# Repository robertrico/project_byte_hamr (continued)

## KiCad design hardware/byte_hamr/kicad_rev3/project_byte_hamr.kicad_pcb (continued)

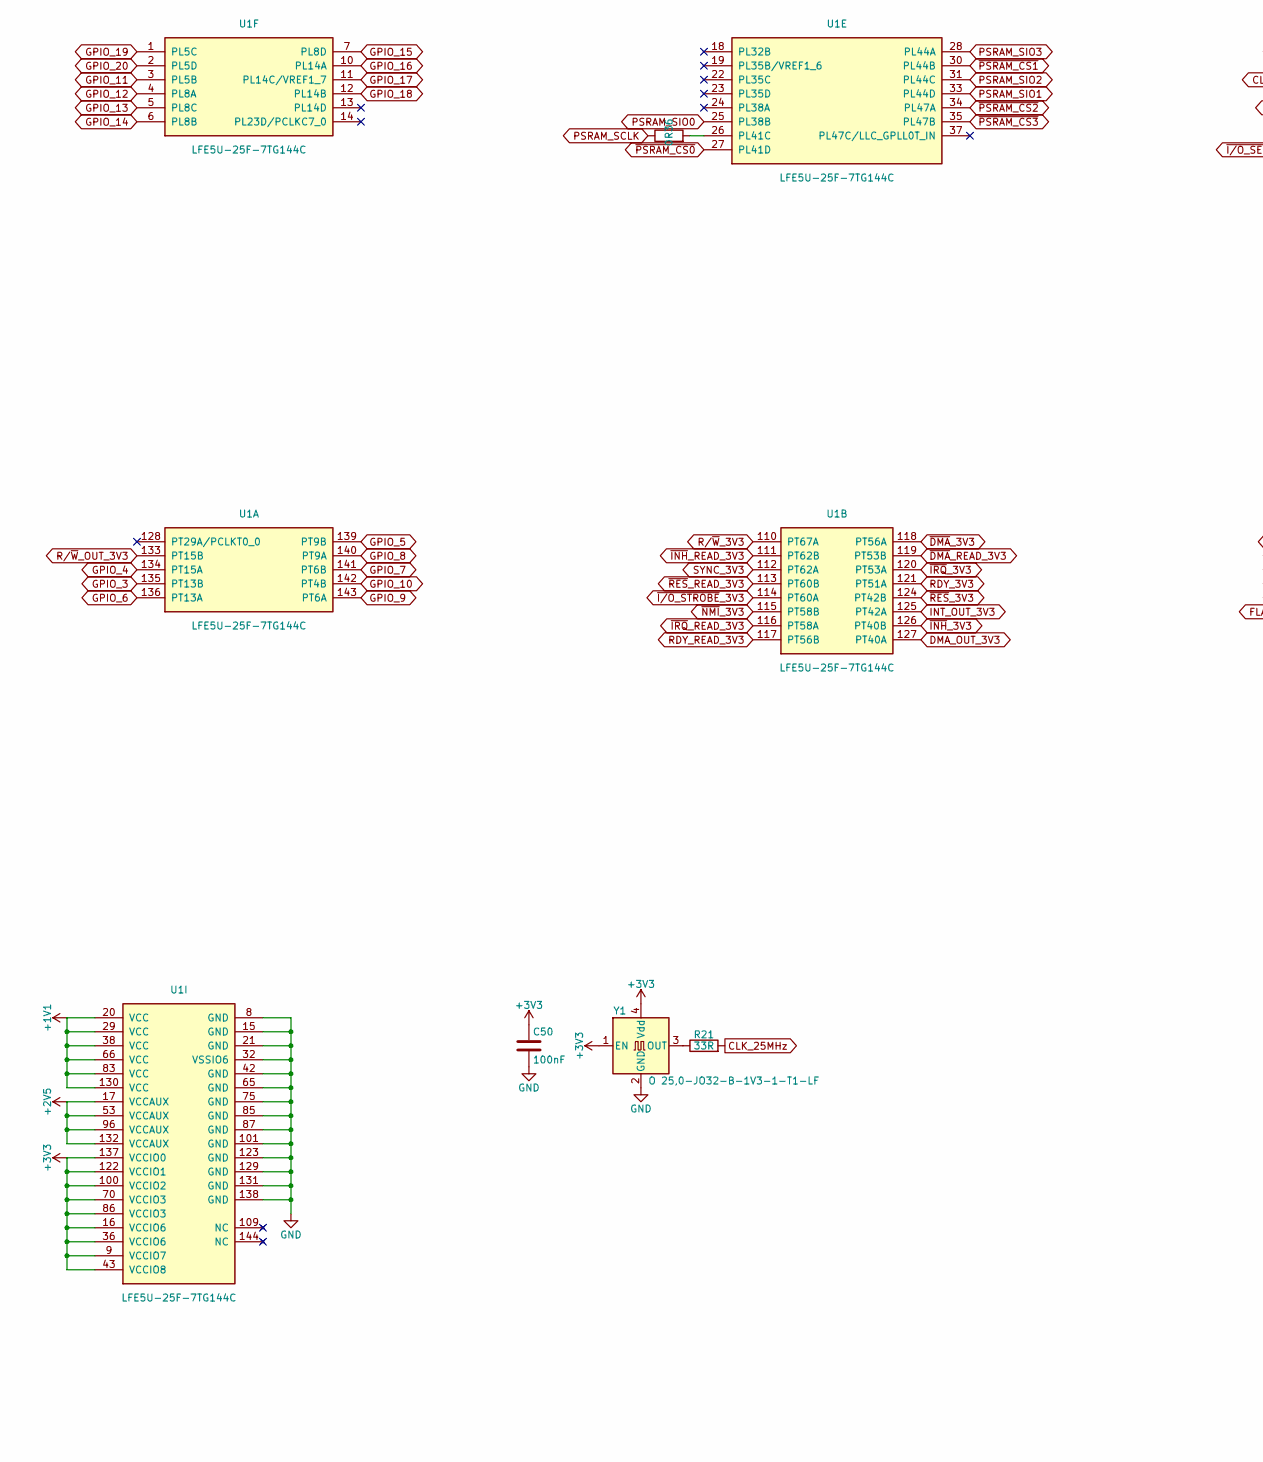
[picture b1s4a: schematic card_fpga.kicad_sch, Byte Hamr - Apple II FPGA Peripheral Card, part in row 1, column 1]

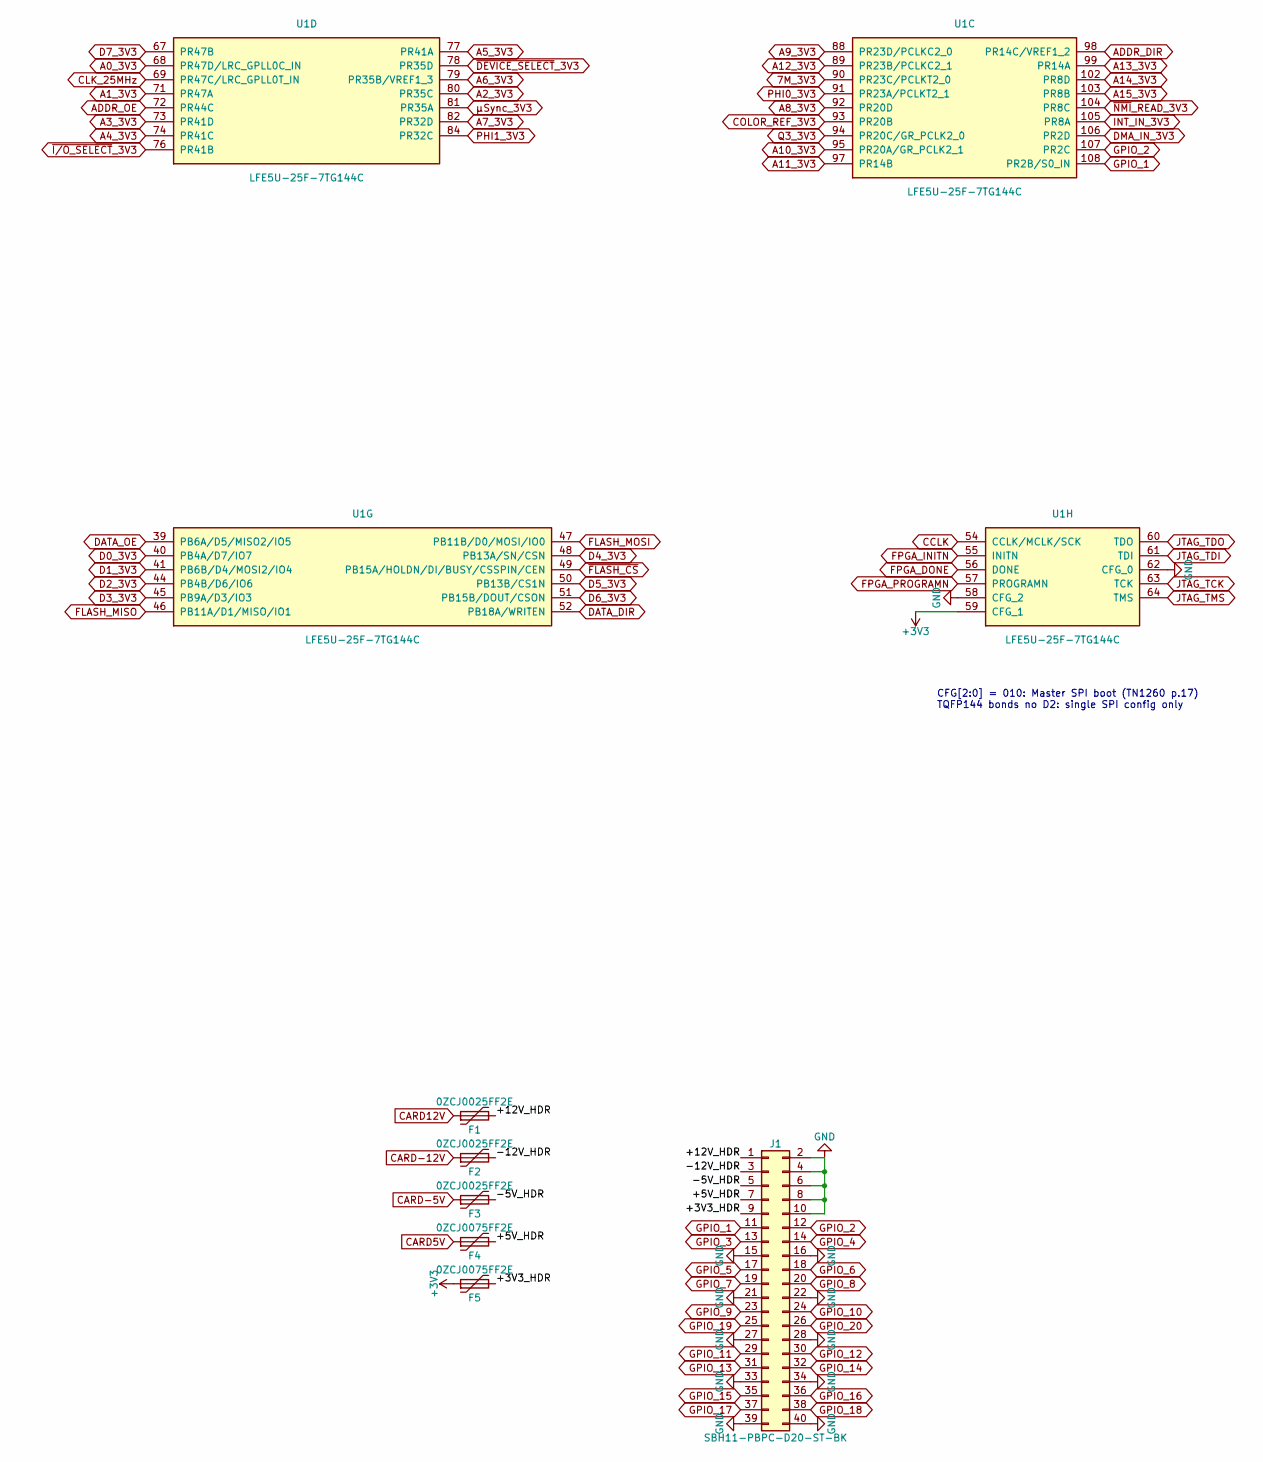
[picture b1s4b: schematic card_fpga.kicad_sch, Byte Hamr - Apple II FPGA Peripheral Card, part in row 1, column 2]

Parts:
C50: 100nF; C_1206_3216Metric; MPN CL31B104KBCNNNC; DigiKey 1276-1017-1-ND
F1, F2, F3: 0ZCJ0025FF2E; Fuse_1206_3216Metric; MPN 0ZCJ0025FF2E; DigiKey 5923-0ZCJ0025FF2ECT-ND
F4, F5: 0ZCJ0075FF2E; Fuse_1206_3216Metric; MPN 0ZCJ0075FF2E; DigiKey 5923-0ZCJ0075FF2ECT-ND
J1: SBH11-PBPC-D20-ST-BK; IDC-Header_2x20_P2.54mm_Vertical; MPN SBH11-PBPC-D20-ST-BK; DigiKey S9175-ND
R21: 33R; R_1206_3216Metric; MPN RMCF1206FT33R0; DigiKey RMCF1206FT33R0CT-ND
R36: 0; R_1206_3216Metric; MPN RMCF1206ZT0R00
U1: LFE5U-25F-7TG144C; LQFP-144_20x20mm_P0.5mm; MPN LFE5U-25F-7TG144C; DigiKey 220-LFE5U-25F-7TG144C-ND
Y1: O 25,0-JO32-B-1V3-1-T1-LF; Crystal_SMD_3225-4Pin_3.2x2.5mm; MPN O 25,0-JO32-B-1V3-1-T1-LF; DigiKey 1908-O250-JO32-B-1V3-1-T1-LFCT-ND

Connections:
7M_3V3: U1.90 (PR23C/PCLKT2_0); also elsewhere on the board
+1V1: U1.20 (VCC), U1.29 (VCC), U1.38 (VCC), U1.66 (VCC), U1.83 (VCC), U1.130 (VCC); also elsewhere on the board
+2V5: U1.17 (VCCAUX), U1.53 (VCCAUX), U1.96 (VCCAUX), U1.132 (VCCAUX); also elsewhere on the board
+3V3: C50.1, F5.1, U1.9 (VCCIO7), U1.16 (VCCIO6), U1.36 (VCCIO6), U1.43 (VCCIO8), U1.59 (CFG_1), U1.70 (VCCIO3), U1.86 (VCCIO3), U1.100 (VCCIO2), U1.122 (VCCIO1), U1.137 (VCCIO0), Y1.1 (EN), Y1.4 (Vdd); also elsewhere on the board
/card_fpga/+3V3_HDR: F5.2, J1.9
/card_fpga/+5V_HDR: F4.2, J1.7
/card_fpga/+12V_HDR: F1.2, J1.1
/card_fpga/-5V_HDR: F3.2, J1.5
/card_fpga/-12V_HDR: F2.2, J1.3
A0_3V3: U1.68 (PR47D/LRC_GPLL0C_IN); also elsewhere on the board
A1_3V3: U1.71 (PR47A); also elsewhere on the board
A2_3V3: U1.80 (PR35C); also elsewhere on the board
A3_3V3: U1.73 (PR41D); also elsewhere on the board
A4_3V3: U1.74 (PR41C); also elsewhere on the board
A5_3V3: U1.77 (PR41A); also elsewhere on the board
A6_3V3: U1.79 (PR35B/VREF1_3); also elsewhere on the board
A7_3V3: U1.82 (PR32D); also elsewhere on the board
A8_3V3: U1.92 (PR20D); also elsewhere on the board
A9_3V3: U1.88 (PR23D/PCLKC2_0); also elsewhere on the board
A10_3V3: U1.95 (PR20A/GR_PCLK2_1); also elsewhere on the board
A11_3V3: U1.97 (PR14B); also elsewhere on the board
A12_3V3: U1.89 (PR23B/PCLKC2_1); also elsewhere on the board
A13_3V3: U1.99 (PR14A); also elsewhere on the board
A14_3V3: U1.102 (PR8D); also elsewhere on the board
A15_3V3: U1.103 (PR8B); also elsewhere on the board
ADDR_DIR: U1.98 (PR14C/VREF1_2); also elsewhere on the board
ADDR_OE: U1.72 (PR44C); also elsewhere on the board
CARD5V: F4.1; also elsewhere on the board
CARD12V: F1.1; also elsewhere on the board
CARD-5V: F3.1; also elsewhere on the board
CARD-12V: F2.1; also elsewhere on the board
CCLK: U1.54 (CCLK/MCLK/SCK); also elsewhere on the board
CLK_25MHz: R21.2, U1.69 (PR47C/LRC_GPLL0T_IN)
COLOR_REF_3V3: U1.93 (PR20B); also elsewhere on the board
D0_3V3: U1.40 (PB4A/D7/IO7); also elsewhere on the board
D1_3V3: U1.41 (PB6B/D4/MOSI2/IO4); also elsewhere on the board
D2_3V3: U1.44 (PB4B/D6/IO6); also elsewhere on the board
D3_3V3: U1.45 (PB9A/D3/IO3); also elsewhere on the board
D4_3V3: U1.48 (PB13A/SN/CSN); also elsewhere on the board
D5_3V3: U1.50 (PB13B/CS1N); also elsewhere on the board
D6_3V3: U1.51 (PB15B/DOUT/CSON); also elsewhere on the board
D7_3V3: U1.67 (PR47B); also elsewhere on the board
DATA_DIR: U1.52 (PB18A/WRITEN); also elsewhere on the board
DATA_OE: U1.39 (PB6A/D5/MISO2/IO5); also elsewhere on the board
DMA_IN_3V3: U1.106 (PR2D); also elsewhere on the board
DMA_OUT_3V3: U1.127 (PT40A); also elsewhere on the board
FLASH_MISO: U1.46 (PB11A/D1/MISO/IO1); also elsewhere on the board
FLASH_MOSI: U1.47 (PB11B/D0/MOSI/IO0); also elsewhere on the board
FPGA_DONE: U1.56 (DONE); also elsewhere on the board
FPGA_INITN: U1.55 (INITN); also elsewhere on the board
FPGA_PROGRAMN: U1.57 (PROGRAMN); also elsewhere on the board
GND: C50.2, J1.2, J1.4, J1.6, J1.8, J1.10, J1.15, J1.16, J1.21, J1.22, J1.27, J1.28, J1.33, J1.34, J1.39, J1.40, U1.8 (GND), U1.15 (GND), U1.21 (GND), U1.32 (VSSIO6), U1.42 (GND), U1.58 (CFG_2), U1.62 (CFG_0), U1.65 (GND), U1.75 (GND), U1.85 (GND), U1.87 (GND), U1.101 (GND), U1.123 (GND), U1.129 (GND), U1.131 (GND), U1.138 (GND), Y1.2 (GND); also elsewhere on the board
GPIO_1: J1.11, U1.108 (PR2B/S0_IN)
GPIO_2: J1.12, U1.107 (PR2C)
GPIO_3: J1.13, U1.135 (PT13B)
GPIO_4: J1.14, U1.134 (PT15A)
GPIO_5: J1.17, U1.139 (PT9B)
GPIO_6: J1.18, U1.136 (PT13A)
GPIO_7: J1.19, U1.141 (PT6B)
GPIO_8: J1.20, U1.140 (PT9A)
GPIO_9: J1.23, U1.143 (PT6A)
GPIO_10: J1.24, U1.142 (PT4B)
GPIO_11: J1.29, U1.3 (PL5B)
GPIO_12: J1.30, U1.4 (PL8A)
GPIO_13: J1.31, U1.5 (PL8C)
GPIO_14: J1.32, U1.6 (PL8B)
GPIO_15: J1.35, U1.7 (PL8D)
GPIO_16: J1.36, U1.10 (PL14A)
GPIO_17: J1.37, U1.11 (PL14C/VREF1_7)
GPIO_18: J1.38, U1.12 (PL14B)
GPIO_19: J1.25, U1.1 (PL5C)
GPIO_20: J1.26, U1.2 (PL5D)
INT_IN_3V3: U1.105 (PR8A); also elsewhere on the board
INT_OUT_3V3: U1.125 (PT42A); also elsewhere on the board
JTAG_TCK: U1.63 (TCK); also elsewhere on the board
JTAG_TDI: U1.61 (TDI); also elsewhere on the board
JTAG_TDO: U1.60 (TDO); also elsewhere on the board
JTAG_TMS: U1.64 (TMS); also elsewhere on the board
unnamed: R36.2, U1.26 (PL41C)
unnamed: R21.1, Y1.3 (OUT)
PHI0_3V3: U1.91 (PR23A/PCLKT2_1); also elsewhere on the board
PHI1_3V3: U1.84 (PR32C); also elsewhere on the board
PSRAM_SCLK: R36.1; also elsewhere on the board
PSRAM_SIO0: U1.25 (PL38B); also elsewhere on the board
PSRAM_SIO1: U1.33 (PL44D); also elsewhere on the board
PSRAM_SIO2: U1.31 (PL44C); also elsewhere on the board
PSRAM_SIO3: U1.28 (PL44A); also elsewhere on the board
Q3_3V3: U1.94 (PR20C/GR_PCLK2_0); also elsewhere on the board
RDY_3V3: U1.121 (PT51A); also elsewhere on the board
RDY_READ_3V3: U1.117 (PT56B); also elsewhere on the board
R/~W_3V3: U1.110 (PT67A); also elsewhere on the board
R/~W_OUT_3V3: U1.133 (PT15B); also elsewhere on the board
SYNC_3V3: U1.112 (PT62A); also elsewhere on the board
~DEVICE_SELECT_3V3: U1.78 (PR35D); also elsewhere on the board
~DMA_3V3: U1.118 (PT56A); also elsewhere on the board
~DMA_READ_3V3: U1.119 (PT53B); also elsewhere on the board
~FLASH_CS: U1.49 (PB15A/HOLDN/DI/BUSY/CSSPIN/CEN); also elsewhere on the board
~INH_3V3: U1.126 (PT40B); also elsewhere on the board
~INH_READ_3V3: U1.111 (PT62B); also elsewhere on the board
~IRQ_3V3: U1.120 (PT53A); also elsewhere on the board
~IRQ_READ_3V3: U1.116 (PT58A); also elsewhere on the board
~I/O_SELECT_3V3: U1.76 (PR41B); also elsewhere on the board
~I/O_STROBE_3V3: U1.114 (PT60A); also elsewhere on the board
~NMI_3V3: U1.115 (PT58B); also elsewhere on the board
~NMI_READ_3V3: U1.104 (PR8C); also elsewhere on the board
~PSRAM_CS0: U1.27 (PL41D); also elsewhere on the board
~PSRAM_CS1: U1.30 (PL44B); also elsewhere on the board
~PSRAM_CS2: U1.34 (PL47A); also elsewhere on the board
~PSRAM_CS3: U1.35 (PL47B); also elsewhere on the board
~RES_3V3: U1.124 (PT42B); also elsewhere on the board
~RES_READ_3V3: U1.113 (PT60B); also elsewhere on the board
µSync_3V3: U1.81 (PR35A); also elsewhere on the board

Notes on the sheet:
CFG[2:0] = 010: Master SPI boot (TN1260 p.17) TQFP144 bonds no D2: single SPI config only

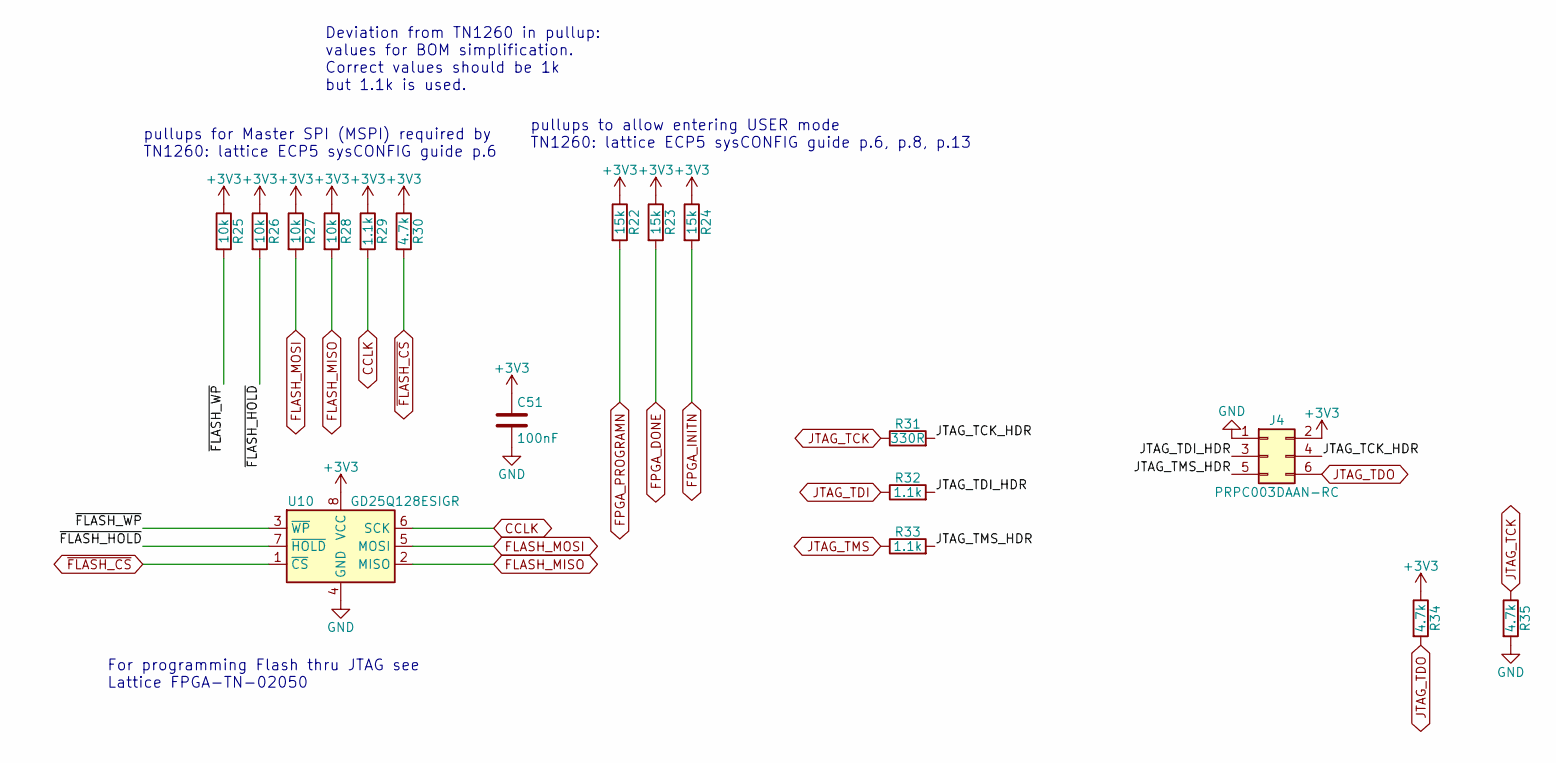
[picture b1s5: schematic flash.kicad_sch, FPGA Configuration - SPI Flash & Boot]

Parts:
C51: 100nF; C_1206_3216Metric; MPN CL31B104KBCNNNC; DigiKey 1276-1017-1-ND
J4: PRPC003DAAN-RC; PinHeader_2x03_P2.54mm_Vertical; MPN PRPC003DAAN-RC; DigiKey 35-PRPC003DAAN-RC-ND
R22, R23, R24: 15k; R_1206_3216Metric; MPN RMCF1206FT15K0; DigiKey RMCF1206FT15K0CT-ND
R25, R26, R27, R28: 10k; R_1206_3216Metric; MPN RMCF1206FT10K0; DigiKey RMCF1206FT10K0CT-ND
R29, R32, R33: 1.1k; R_1206_3216Metric; MPN RMCF1206FT1K10; DigiKey 738-RMCF1206FT1K10CT-ND
R30, R34, R35: 4.7k; R_1206_3216Metric; MPN RMCF1206FT4K70; DigiKey RMCF1206FT4K70CT-ND
R31: 330R; R_1206_3216Metric; MPN RMCF1206FT330R; DigiKey 738-RMCF1206FT330RCT-ND
U10: GD25Q128ESIGR; SOIC-8_5.3x5.3mm_P1.27mm; MPN GD25Q128ESIGR; DigiKey 1970-GD25Q128ESIGRCT-ND

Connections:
+3V3: C51.1, J4.2, R22.1, R23.1, R24.1, R25.1, R26.1, R27.1, R28.1, R29.1, R30.1, R34.1, U10.8 (VCC); also elsewhere on the board
/flash/JTAG_TCK_HDR: J4.4, R31.2
/flash/JTAG_TDI_HDR: J4.3, R32.2
/flash/JTAG_TMS_HDR: J4.5, R33.2
/flash/~FLASH_HOLD: R26.2, U10.7 (~HOLD)
/flash/~FLASH_WP: R25.2, U10.3 (~WP)
CCLK: R29.2, U10.6 (SCK); also elsewhere on the board
FLASH_MISO: R28.2, U10.2 (MISO); also elsewhere on the board
FLASH_MOSI: R27.2, U10.5 (MOSI); also elsewhere on the board
FPGA_DONE: R23.2; also elsewhere on the board
FPGA_INITN: R24.2; also elsewhere on the board
FPGA_PROGRAMN: R22.2; also elsewhere on the board
GND: C51.2, J4.1, R35.2, U10.4 (GND); also elsewhere on the board
JTAG_TCK: R31.1, R35.1; also elsewhere on the board
JTAG_TDI: R32.1; also elsewhere on the board
JTAG_TDO: J4.6, R34.2; also elsewhere on the board
JTAG_TMS: R33.1; also elsewhere on the board
~FLASH_CS: R30.2, U10.1 (~CS); also elsewhere on the board

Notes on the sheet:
pullups to allow entering USER mode TN1260: lattice ECP5 sysCONFIG guide p.6, p.8, p.13
pullups for Master SPI (MSPI) required by TN1260: lattice ECP5 sysCONFIG guide p.6
Deviation from TN1260 in pullup: values for BOM simplification. Correct values should be 1k but 1.1k is used.
For programming Flash thru JTAG see Lattice FPGA-TN-02050

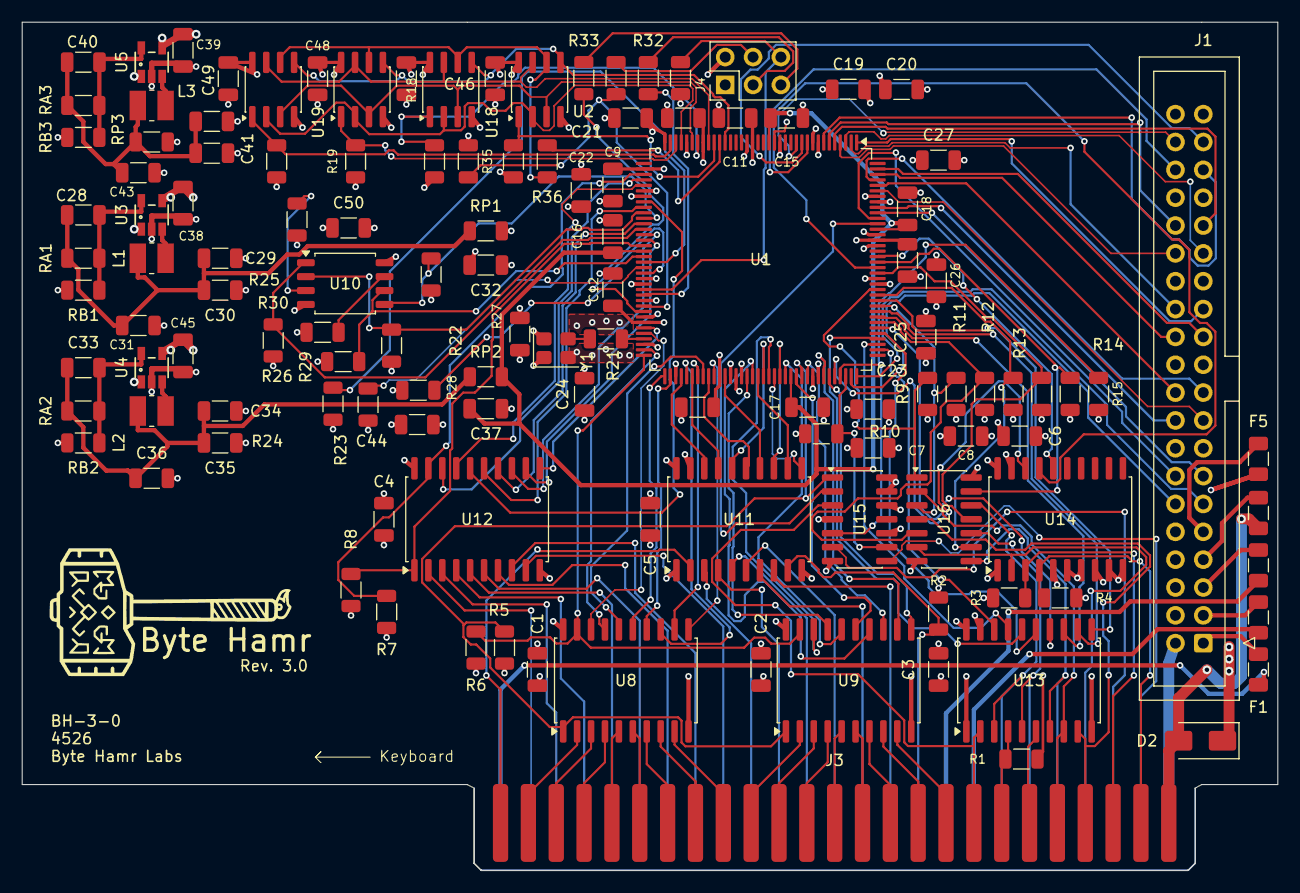
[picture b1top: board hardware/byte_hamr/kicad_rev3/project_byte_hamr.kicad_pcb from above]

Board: 4 copper layers, 114.5 x 77.4 mm, 126 parts (0 on the bottom side), 172 nets.

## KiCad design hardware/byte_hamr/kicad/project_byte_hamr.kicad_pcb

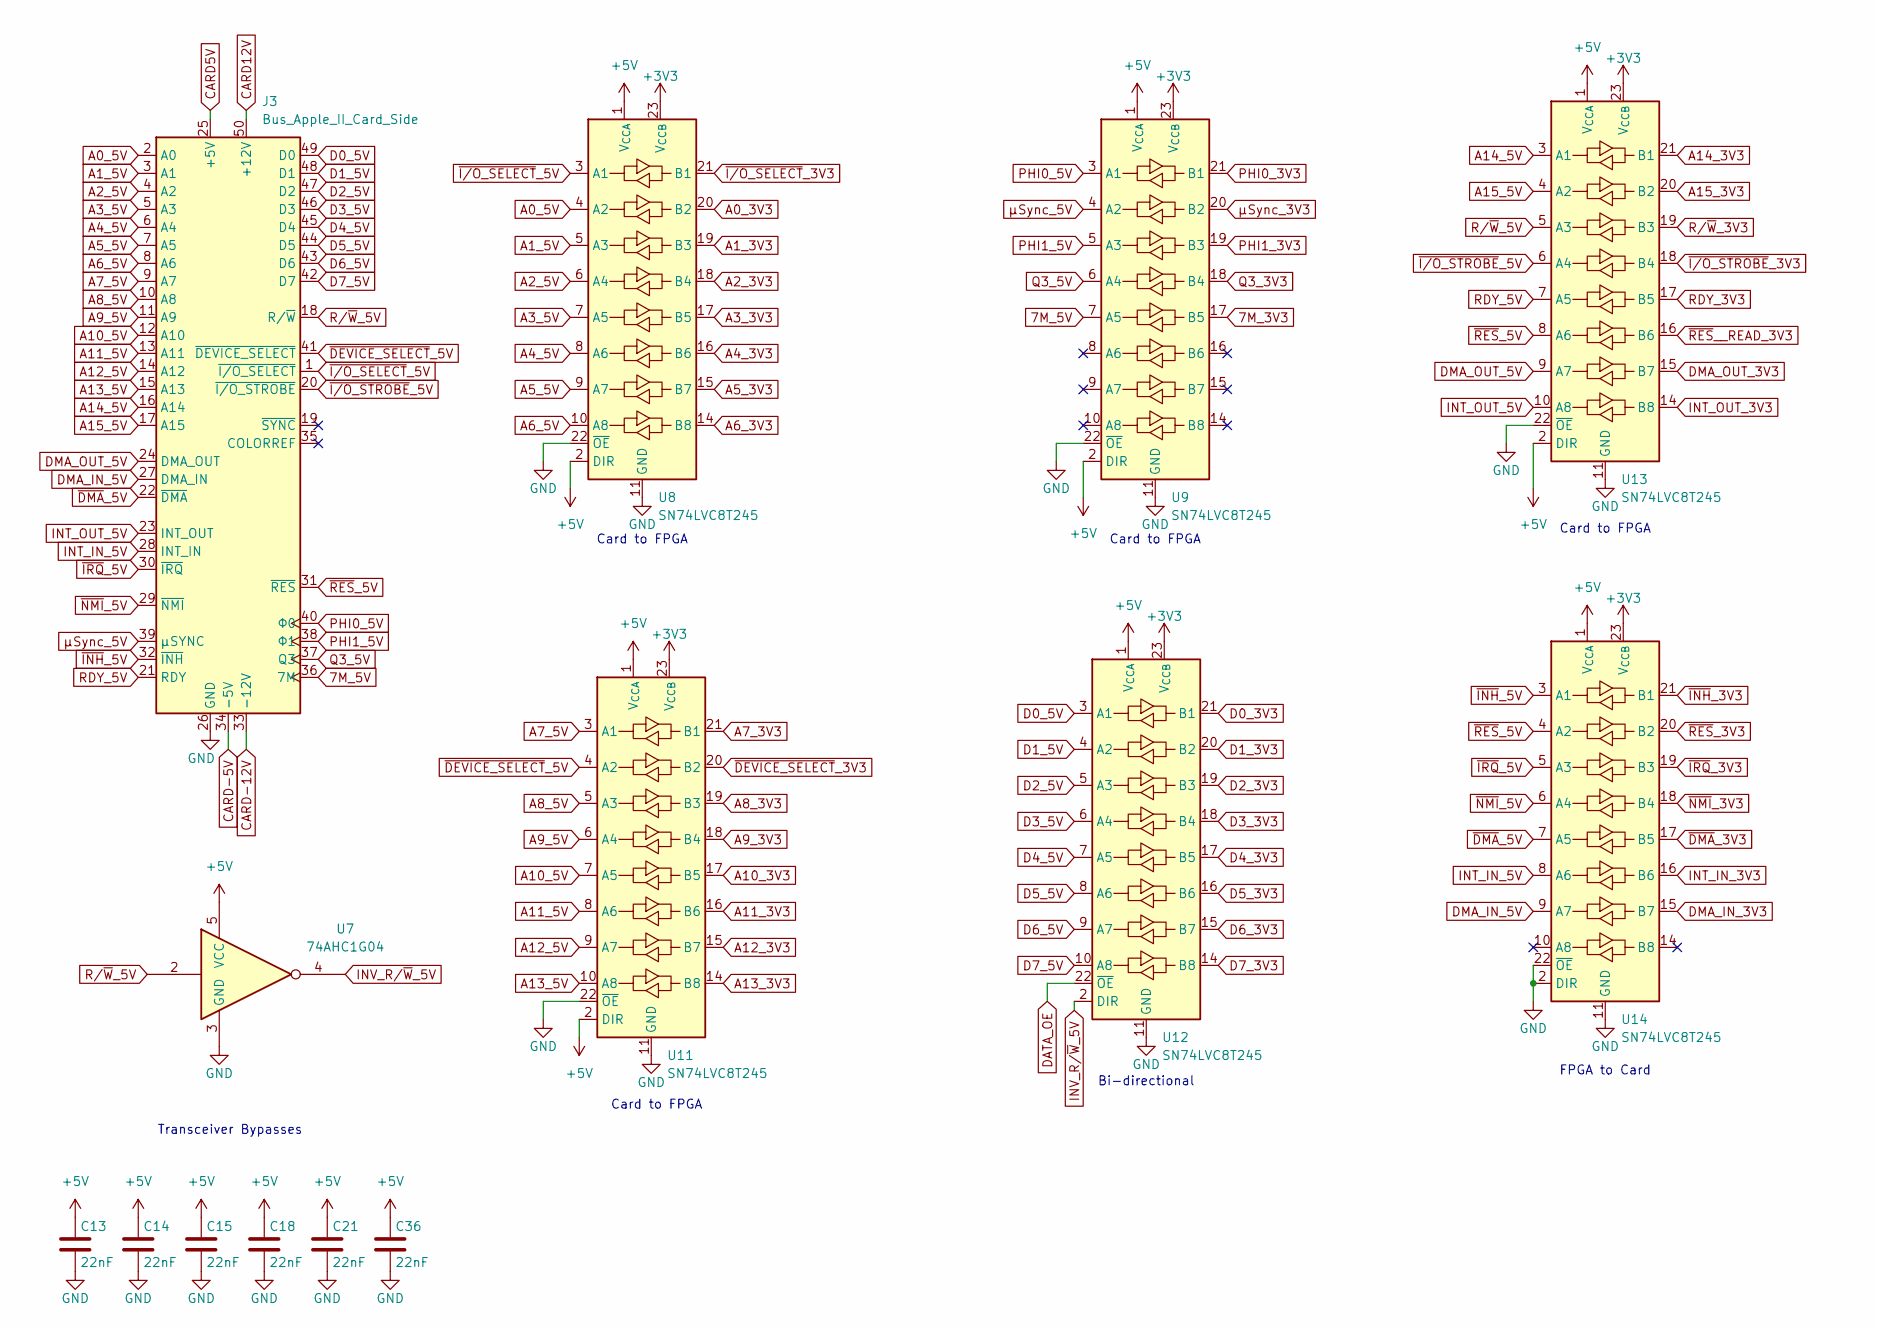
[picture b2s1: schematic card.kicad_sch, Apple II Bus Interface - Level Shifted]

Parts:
C13, C14, C15, C18, C21, C36: 22nF; C_0603_1608Metric; MPN CX0603MRX7R8BB223
J3: Bus_Apple_II_Card_Side; Peripheral_Bus_Edge
U7: 74AHC1G04; SOT95P280X145-5N; MPN SN74LVC1G04DBVR
U8, U9, U11, U12, U13, U14: SN74LVC8T245; DBQ24-L; MPN SN74LVC8T245DBQR

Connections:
7M_3V3: U9.17 (B5); also elsewhere on the board
7M_5V: J3.36 (7M), U9.7 (A5)
+3V3: U8.23 (V_{CCB}), U8.24 (V_{CCB}), U9.23 (V_{CCB}), U9.24 (V_{CCB}), U11.23 (V_{CCB}), U11.24 (V_{CCB}), U12.23 (V_{CCB}), U12.24 (V_{CCB}), U13.23 (V_{CCB}), U13.24 (V_{CCB}), U14.23 (V_{CCB}), U14.24 (V_{CCB}); also elsewhere on the board
+5V: C13.1, C14.1, C15.1, C18.1, C21.1, C36.1, U7.5 (VCC), U8.1 (V_{CCA}), U8.2 (DIR), U9.1 (V_{CCA}), U9.2 (DIR), U11.1 (V_{CCA}), U11.2 (DIR), U12.1 (V_{CCA}), U13.1 (V_{CCA}), U13.2 (DIR), U14.1 (V_{CCA}); also elsewhere on the board
A0_3V3: U8.20 (B2); also elsewhere on the board
A0_5V: J3.2 (A0), U8.4 (A2)
A1_3V3: U8.19 (B3); also elsewhere on the board
A1_5V: J3.3 (A1), U8.5 (A3)
A2_3V3: U8.18 (B4); also elsewhere on the board
A2_5V: J3.4 (A2), U8.6 (A4)
A3_3V3: U8.17 (B5); also elsewhere on the board
A3_5V: J3.5 (A3), U8.7 (A5)
A4_3V3: U8.16 (B6); also elsewhere on the board
A4_5V: J3.6 (A4), U8.8 (A6)
A5_3V3: U8.15 (B7); also elsewhere on the board
A5_5V: J3.7 (A5), U8.9 (A7)
A6_3V3: U8.14 (B8); also elsewhere on the board
A6_5V: J3.8 (A6), U8.10 (A8)
A7_3V3: U11.21 (B1); also elsewhere on the board
A7_5V: J3.9 (A7), U11.3 (A1)
A8_3V3: U11.19 (B3); also elsewhere on the board
A8_5V: J3.10 (A8), U11.5 (A3)
A9_3V3: U11.18 (B4); also elsewhere on the board
A9_5V: J3.11 (A9), U11.6 (A4)
A10_3V3: U11.17 (B5); also elsewhere on the board
A10_5V: J3.12 (A10), U11.7 (A5)
A11_3V3: U11.16 (B6); also elsewhere on the board
A11_5V: J3.13 (A11), U11.8 (A6)
A12_3V3: U11.15 (B7); also elsewhere on the board
A12_5V: J3.14 (A12), U11.9 (A7)
A13_3V3: U11.14 (B8); also elsewhere on the board
A13_5V: J3.15 (A13), U11.10 (A8)
A14_3V3: U13.21 (B1); also elsewhere on the board
A14_5V: J3.16 (A14), U13.3 (A1)
A15_3V3: U13.20 (B2); also elsewhere on the board
A15_5V: J3.17 (A15), U13.4 (A2)
CARD5V: J3.25 (+5V); also elsewhere on the board
CARD12V: J3.50 (+12V); also elsewhere on the board
CARD-5V: J3.34 (-5V); also elsewhere on the board
CARD-12V: J3.33 (-12V); also elsewhere on the board
D0_3V3: U12.21 (B1); also elsewhere on the board
D0_5V: J3.49 (D0), U12.3 (A1)
D1_3V3: U12.20 (B2); also elsewhere on the board
D1_5V: J3.48 (D1), U12.4 (A2)
D2_3V3: U12.19 (B3); also elsewhere on the board
D2_5V: J3.47 (D2), U12.5 (A3)
D3_3V3: U12.18 (B4); also elsewhere on the board
D3_5V: J3.46 (D3), U12.6 (A4)
D4_3V3: U12.17 (B5); also elsewhere on the board
D4_5V: J3.45 (D4), U12.7 (A5)
D5_3V3: U12.16 (B6); also elsewhere on the board
D5_5V: J3.44 (D5), U12.8 (A6)
D6_3V3: U12.15 (B7); also elsewhere on the board
D6_5V: J3.43 (D6), U12.9 (A7)
D7_3V3: U12.14 (B8); also elsewhere on the board
D7_5V: J3.42 (D7), U12.10 (A8)
DATA_OE: U12.22 (~OE); also elsewhere on the board
DMA_IN_3V3: U14.15 (B7); also elsewhere on the board
DMA_IN_5V: J3.27 (DMA_IN), U14.9 (A7)
DMA_OUT_3V3: U13.15 (B7); also elsewhere on the board
DMA_OUT_5V: J3.24 (DMA_OUT), U13.9 (A7)
GND: C13.2, C14.2, C15.2, C18.2, C21.2, C36.2, J3.26 (GND), U7.3 (GND), U8.11 (GND), U8.12 (GND), U8.13 (GND), U8.22 (~OE), U9.11 (GND), U9.12 (GND), U9.13 (GND), U9.22 (~OE), U11.11 (GND), U11.12 (GND), U11.13 (GND), U11.22 (~OE), U12.11 (GND), U12.12 (GND), U12.13 (GND), U13.11 (GND), U13.12 (GND), U13.13 (GND), U13.22 (~OE), U14.2 (DIR), U14.11 (GND), U14.12 (GND), U14.13 (GND), U14.22 (~OE); also elsewhere on the board
INT_IN_3V3: U14.16 (B6); also elsewhere on the board
INT_IN_5V: J3.28 (INT_IN), U14.8 (A6)
INT_OUT_3V3: U13.14 (B8); also elsewhere on the board
INT_OUT_5V: J3.23 (INT_OUT), U13.10 (A8)
INV_R/~W_5V: U7.4, U12.2 (DIR)
PHI0_3V3: U9.21 (B1); also elsewhere on the board
PHI0_5V: J3.40 (Φ0), U9.3 (A1)
PHI1_3V3: U9.19 (B3); also elsewhere on the board
PHI1_5V: J3.38 (Φ1), U9.5 (A3)
Q3_3V3: U9.18 (B4); also elsewhere on the board
Q3_5V: J3.37 (Q3), U9.6 (A4)
RDY_3V3: U13.17 (B5); also elsewhere on the board
RDY_5V: J3.21 (RDY), U13.7 (A5)
R/~W_3V3: U13.19 (B3); also elsewhere on the board
R/~W_5V: J3.18 (R/~W), U7.2, U13.5 (A3)
~DEVICE_SELECT_3V3: U11.20 (B2); also elsewhere on the board
~DEVICE_SELECT_5V: J3.41 (~DEVICE_SELECT), U11.4 (A2)
~DMA_3V3: U14.17 (B5); also elsewhere on the board
~DMA_5V: J3.22 (~DMA), U14.7 (A5)
~INH_3V3: U14.21 (B1); also elsewhere on the board
~INH_5V: J3.32 (~INH), U14.3 (A1)
~IRQ_3V3: U14.19 (B3); also elsewhere on the board
~IRQ_5V: J3.30 (~IRQ), U14.5 (A3)
~I/O_SELECT_3V3: U8.21 (B1); also elsewhere on the board
~I/O_SELECT_5V: J3.1 (~I/O_SELECT), U8.3 (A1)
~I/O_STROBE_3V3: U13.18 (B4); also elsewhere on the board
~I/O_STROBE_5V: J3.20 (~I/O_STROBE), U13.6 (A4)
~NMI_3V3: U14.18 (B4); also elsewhere on the board
~NMI_5V: J3.29 (~NMI), U14.6 (A4)
~RES_3V3: U14.20 (B2); also elsewhere on the board
~RES_5V: J3.31 (~RES), U13.8 (A6), U14.4 (A2)
~RES__READ_3V3: U13.16 (B6); also elsewhere on the board
µSync_3V3: U9.20 (B2); also elsewhere on the board
µSync_5V: J3.39 (µSYNC), U9.4 (A2)

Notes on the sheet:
FPGA to Card
Card to FPGA
Transceiver Bypasses
Bi-directional

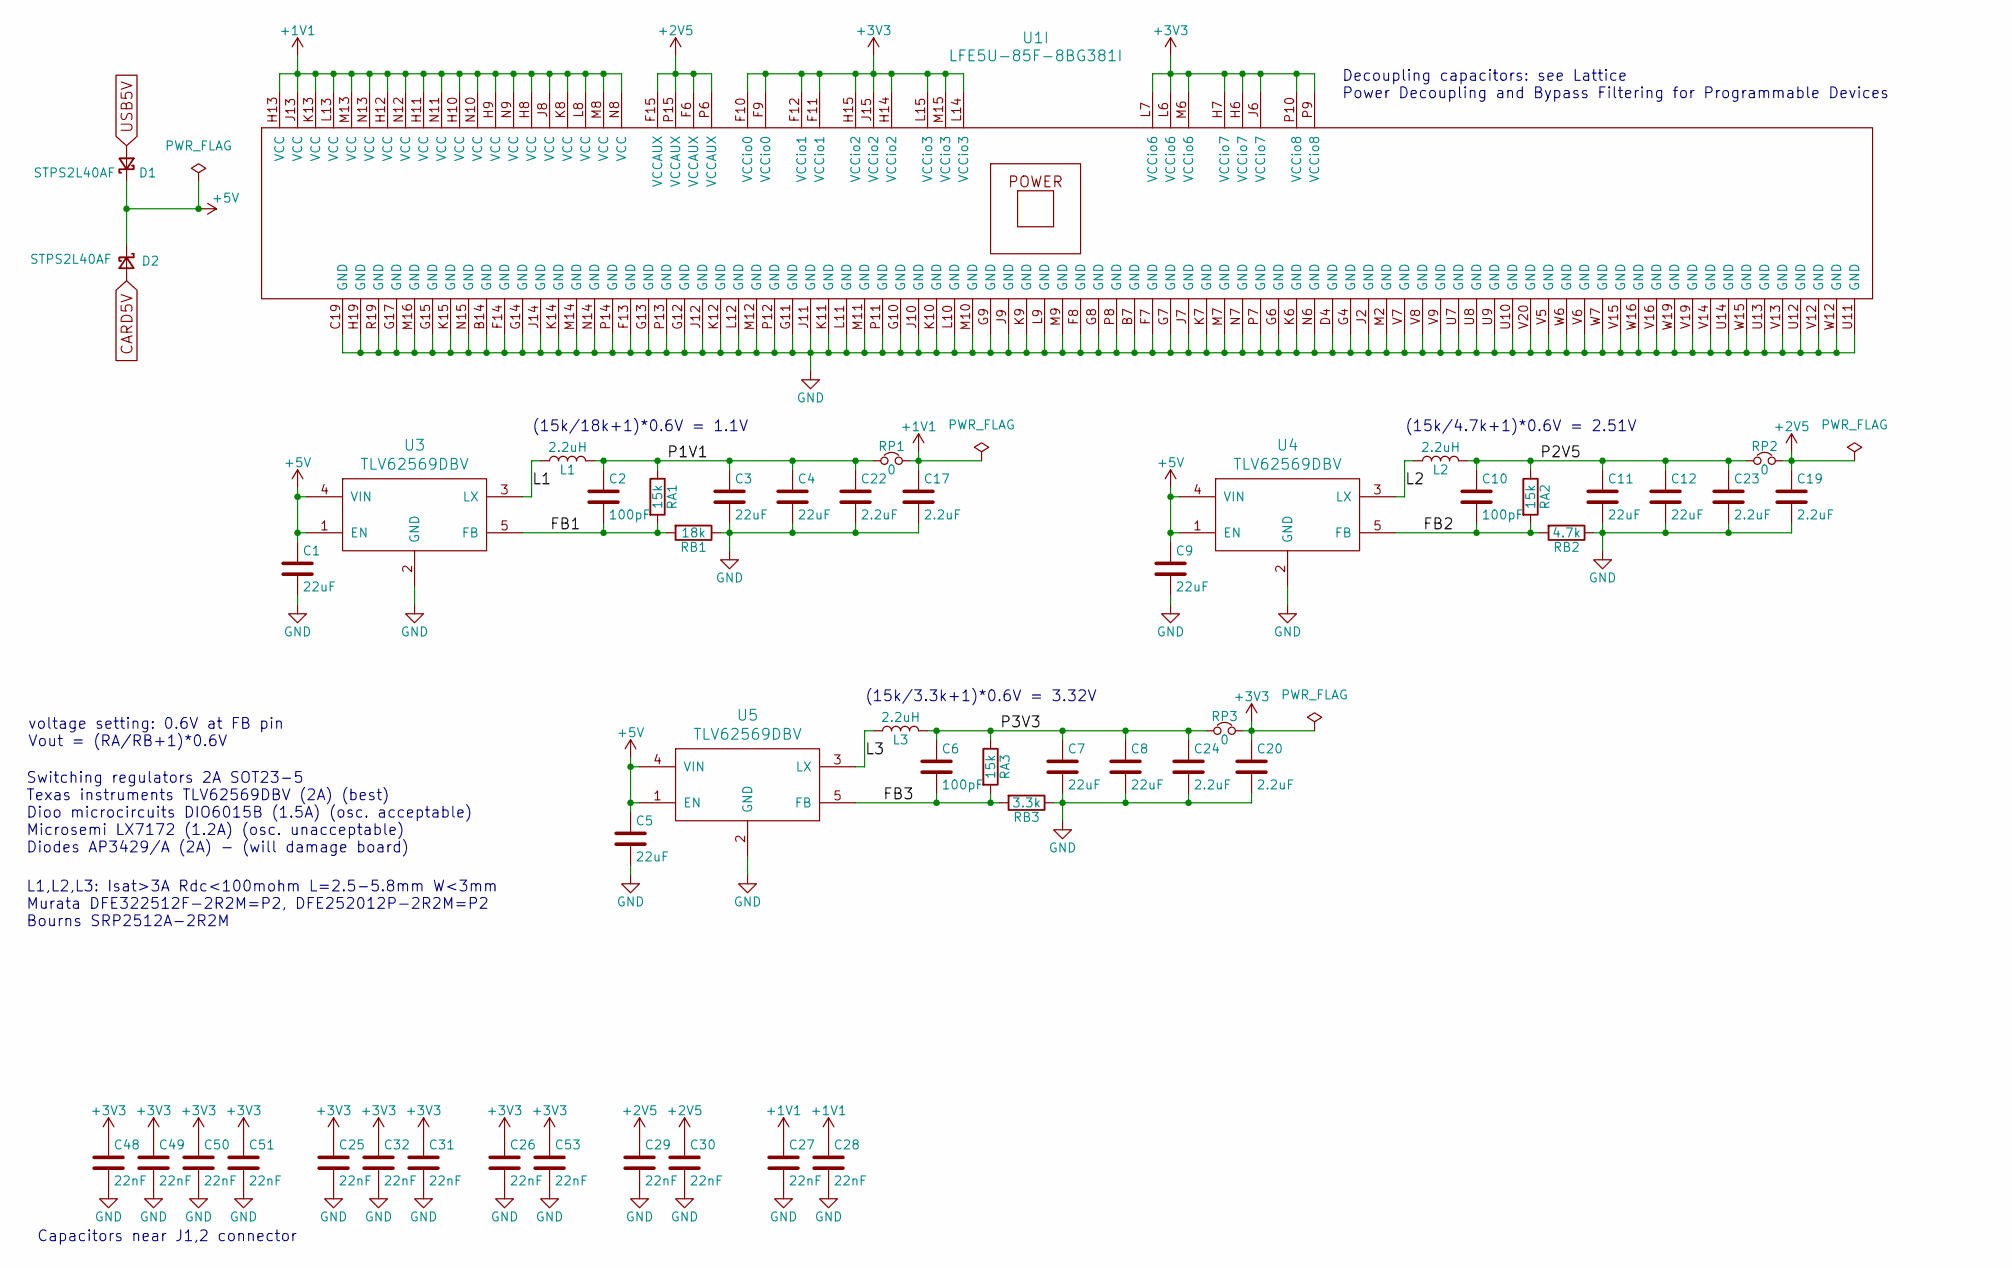
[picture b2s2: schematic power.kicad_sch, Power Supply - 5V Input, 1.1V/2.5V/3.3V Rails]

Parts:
C1, C3, C4, C5, C7, C8, C9, C11, C12: 22uF; C_0805_2012Metric; MPN CL21A226MQQNNNE
C2, C6, C10: 100pF; C_0603_1608Metric; MPN FH 0603CG101J500NT
C17, C19, C20, C22, C23, C24: 2.2uF; C_0805_2012Metric; MPN CL21B225KOFNNNE
C25, C26, C27, C28, C29, C30, C31, C32, C48, C49, C50, C51, C53: 22nF; C_0603_1608Metric; MPN CX0603MRX7R8BB223
D1, D2: STPS2L40AF; D_SMA; MPN STPS2L40AF
L1, L2, L3: 2.2uH; L_1008_1210; MPN DFE322520FD-2R2M=P2
RA1, RA2, RA3: 15k; R_0603_1608Metric; MPN RC0603FR-0715KL
RB1: 18k; R_0603_1608Metric; MPN RC0603FR-1018KL
RB2: 4.7k; R_0603_1608Metric; MPN AC0603FR-104K7L
RB3: 3.3k; R_0603_1608Metric; MPN RT0603FRE073K3L
RP1, RP2, RP3: 0; R_0805_2012Metric_Pad1.29x1.40mm_HandSolder_Jumper_NC; MPN 0805W8F0000T5E
U1: LFE5U-85F-8BG381I; BGA-381_pitch0.8mm_dia0.4mm; MPN LFE5U-85F-8BG381I
U3, U4, U5: TLV62569DBV; TSOT-25; MPN TLV62569DBVR

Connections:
+1V1: C17.1, C27.1, C28.1, RP1.2, U1.H8 (VCC), U1.H9 (VCC), U1.H10 (VCC), U1.H11 (VCC), U1.H12 (VCC), U1.H13 (VCC), U1.J8 (VCC), U1.J13 (VCC), U1.K8 (VCC), U1.K13 (VCC), U1.L8 (VCC), U1.L13 (VCC), U1.M8 (VCC), U1.M13 (VCC), U1.N8 (VCC), U1.N9 (VCC), U1.N10 (VCC), U1.N11 (VCC), U1.N12 (VCC), U1.N13 (VCC); also elsewhere on the board
+2V5: C19.1, C29.1, C30.1, RP2.2, U1.F6 (VCCAUX), U1.F15 (VCCAUX), U1.P6 (VCCAUX), U1.P15 (VCCAUX)
+3V3: C20.1, C25.1, C26.1, C31.1, C32.1, C48.1, C49.1, C50.1, C51.1, C53.1, RP3.2, U1.F9 (VCCio0), U1.F10 (VCCio0), U1.F11 (VCCio1), U1.F12 (VCCio1), U1.H6 (VCCio7), U1.H7 (VCCio7), U1.H14 (VCCio2), U1.H15 (VCCio2), U1.J6 (VCCio7), U1.J15 (VCCio2), U1.L6 (VCCio6), U1.L7 (VCCio6), U1.L14 (VCCio3), U1.L15 (VCCio3), U1.M6 (VCCio6), U1.M15 (VCCio3), U1.P9 (VCCio8), U1.P10 (VCCio8); also elsewhere on the board
+5V: C1.1, C5.1, C9.1, D1.1 (K), D2.1 (K), U3.1 (EN), U3.4 (VIN), U4.1 (EN), U4.4 (VIN), U5.1 (EN), U5.4 (VIN); also elsewhere on the board
/power/FB1: C2.2, RA1.2, RB1.2, U3.5 (FB)
/power/FB2: C10.2, RA2.2, RB2.2, U4.5 (FB)
/power/FB3: C6.2, RA3.2, RB3.2, U5.5 (FB)
/power/L1: L1.1, U3.3 (LX)
/power/L2: L2.1, U4.3 (LX)
/power/L3: L3.1, U5.3 (LX)
/power/P1V1: C2.1, C3.1, C4.1, C22.1, L1.2, RA1.1, RP1.1
/power/P2V5: C10.1, C11.1, C12.1, C23.1, L2.2, RA2.1, RP2.1
/power/P3V3: C6.1, C7.1, C8.1, C24.1, L3.2, RA3.1, RP3.1
CARD5V: D2.2 (A); also elsewhere on the board
GND: C1.2, C3.2, C4.2, C5.2, C7.2, C8.2, C9.2, C11.2, C12.2, C17.2, C19.2, C20.2, C22.2, C23.2, C24.2, C25.2, C26.2, C27.2, C28.2, C29.2, C30.2, C31.2, C32.2, C48.2, C49.2, C50.2, C51.2, C53.2, RB1.1, RB2.1, RB3.1, U1.B7 (GND), U1.B14 (GND), U1.C19 (GND), U1.D4 (GND), U1.F7 (GND), U1.F8 (GND), U1.F13 (GND), U1.F14 (GND), U1.G4 (GND), U1.G6 (GND), U1.G7 (GND), U1.G8 (GND), U1.G9 (GND), U1.G10 (GND), U1.G11 (GND), U1.G12 (GND), U1.G13 (GND), U1.G14 (GND), U1.G15 (GND), U1.G17 (GND), U1.H19 (GND), U1.J2 (GND), U1.J7 (GND), U1.J9 (GND), U1.J10 (GND), U1.J11 (GND), U1.J12 (GND), U1.J14 (GND), U1.K6 (GND), U1.K7 (GND), U1.K9 (GND), U1.K10 (GND), U1.K11 (GND), U1.K12 (GND), U1.K14 (GND), U1.K15 (GND), U1.L9 (GND), U1.L10 (GND), U1.L11 (GND), U1.L12 (GND), U1.M2 (GND), U1.M7 (GND), U1.M9 (GND), U1.M10 (GND), U1.M11 (GND), U1.M12 (GND), U1.M14 (GND), U1.M16 (GND), U1.N6 (GND), U1.N7 (GND), U1.N14 (GND), U1.N15 (GND), U1.P7 (GND), U1.P8 (GND), U1.P11 (GND), U1.P12 (GND), U1.P13 (GND), U1.P14 (GND), U1.R19 (GND), U1.U7 (GND), U1.U8 (GND), U1.U9 (GND), U1.U10 (GND), U1.U11 (GND), U1.U12 (GND), U1.U13 (GND), U1.U14 (GND), U1.V5 (GND), U1.V6 (GND), U1.V7 (GND), U1.V8 (GND), U1.V9 (GND), U1.V12 (GND), U1.V13 (GND), U1.V14 (GND), U1.V15 (GND), U1.V16 (GND), U1.V19 (GND), U1.V20 (GND), U1.W6 (GND), U1.W7 (GND), U1.W12 (GND), U1.W15 (GND), U1.W16 (GND), U1.W19 (GND), U3.2 (GND), U4.2 (GND), U5.2 (GND); also elsewhere on the board
USB5V: D1.2 (A); also elsewhere on the board

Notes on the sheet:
Switching regulators 2A SOT23-5 Texas instruments TLV62569DBV (2A) (best) Dioo microcircuits DIO6015B (1.5A) (osc. acceptable) Microsemi LX7172 (1.2A) (osc. unacceptable) Diodes AP3429/A (2A) - (will damage board)
(15k/18k+1)*0.6V = 1.1V
L1,L2,L3: Isat>3A Rdc<100mohm L=2.5-5.8mm W<3mm Murata DFE322512F-2R2M=P2, DFE252012P-2R2M=P2 Bourns SRP2512A-2R2M
(15k/4.7k+1)*0.6V = 2.51V
(15k/3.3k+1)*0.6V = 3.32V
Capacitors near J1,2 connector
Decoupling capacitors: see Lattice Power Decoupling and Bypass Filtering for Programmable Devices
voltage setting: 0.6V at FB pin Vout = (RA/RB+1)*0.6V
